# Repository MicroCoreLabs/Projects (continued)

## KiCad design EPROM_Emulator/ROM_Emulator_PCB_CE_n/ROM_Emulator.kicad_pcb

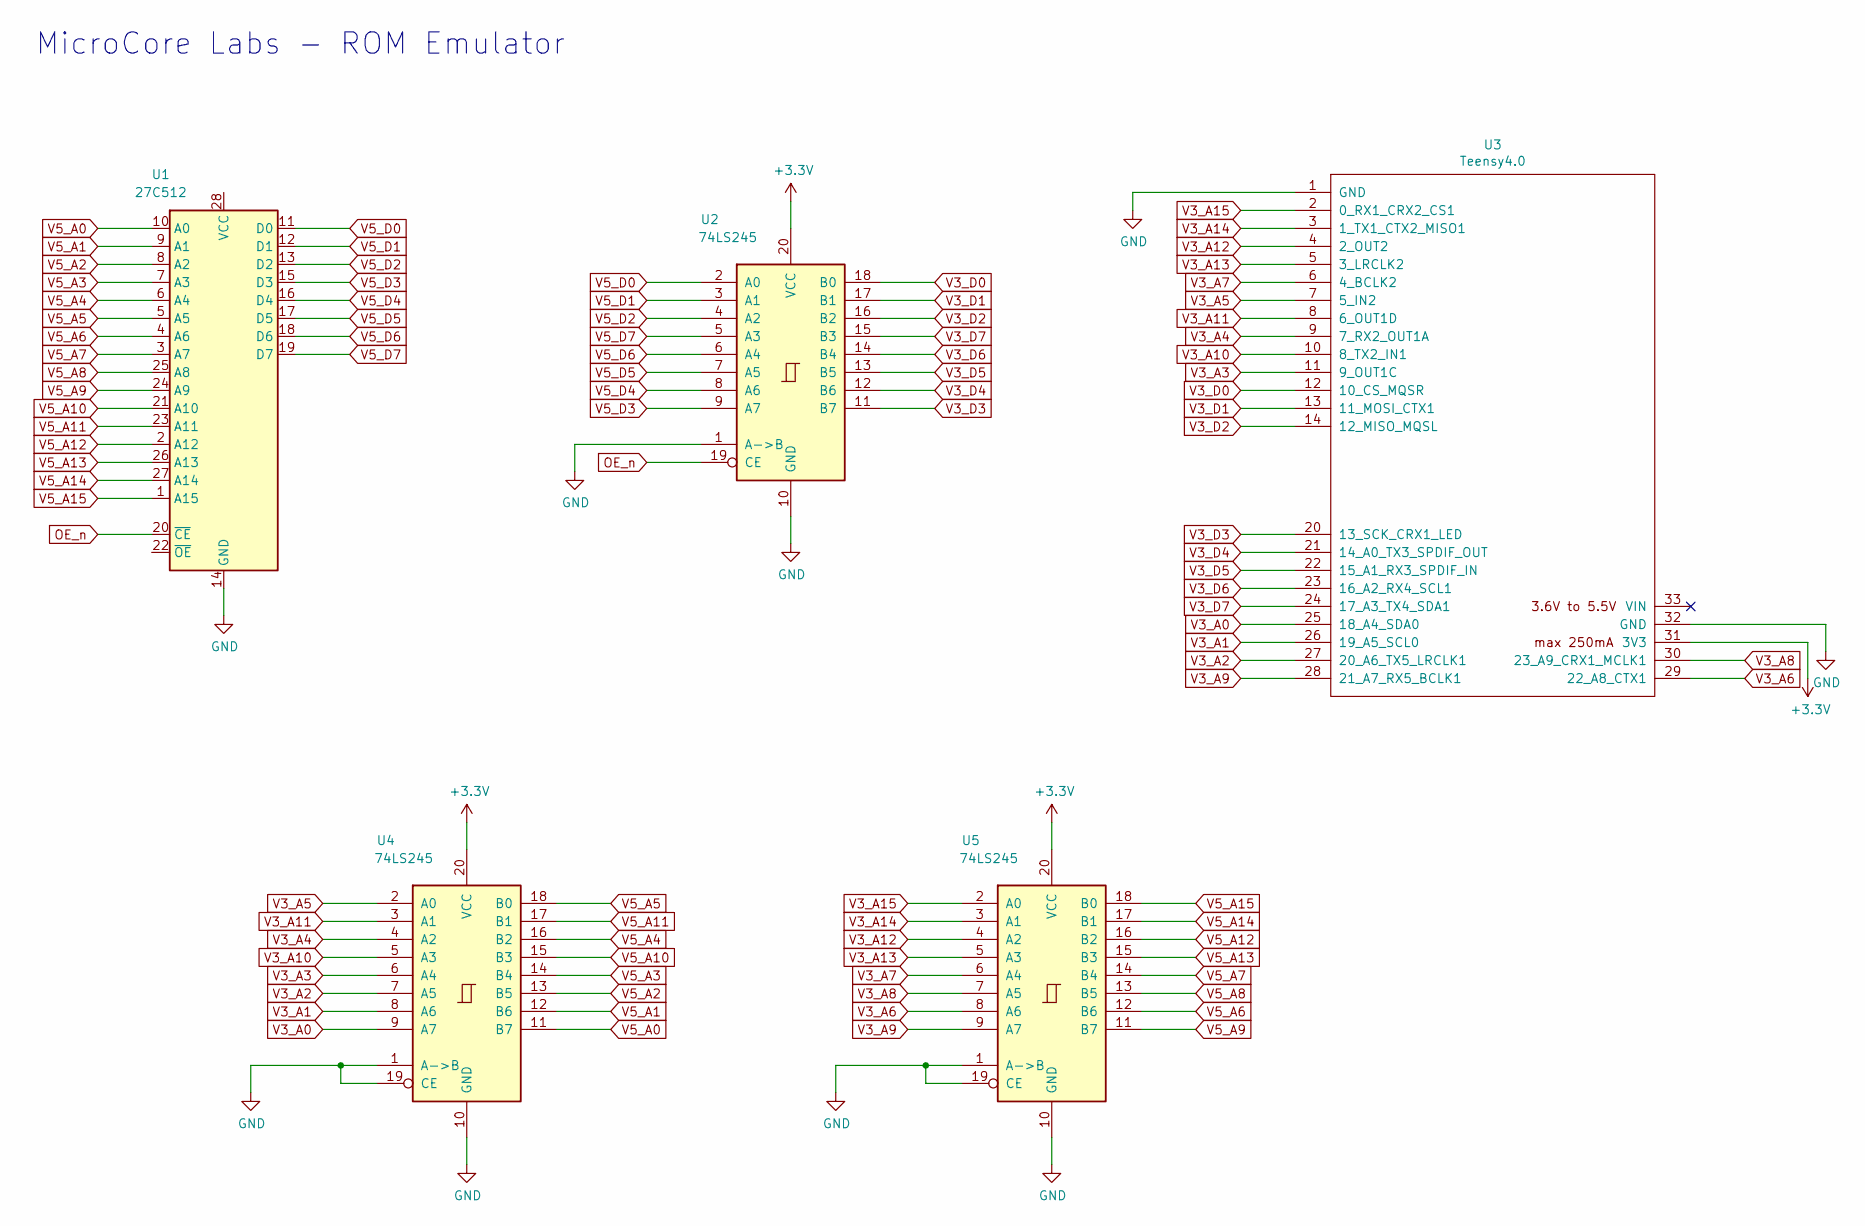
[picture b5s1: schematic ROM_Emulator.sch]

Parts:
U1: 27C512; DIP-28_W15.24mm
U2, U4, U5: 74LS245; SSOP-20_5.3x7.2mm_P0.65mm
U3: Teensy4.0; Teensy40

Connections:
+3V3: U2.20 (VCC), U3.31 (3V3), U4.20 (VCC), U5.20 (VCC)
GND: U1.14 (GND), U2.1 (A->B), U2.10 (GND), U3.1 (GND), U3.32 (GND), U4.1 (A->B), U4.10 (GND), U4.19 (CE), U5.1 (A->B), U5.10 (GND), U5.19 (CE)
OE_n: U1.20 (~CE), U2.19 (CE)
V3_A0: U3.25 (18_A4_SDA0), U4.9 (A7)
V3_A1: U3.26 (19_A5_SCL0), U4.8 (A6)
V3_A2: U3.27 (20_A6_TX5_LRCLK1), U4.7 (A5)
V3_A3: U3.11 (9_OUT1C), U4.6 (A4)
V3_A4: U3.9 (7_RX2_OUT1A), U4.4 (A2)
V3_A5: U3.7 (5_IN2), U4.2 (A0)
V3_A6: U3.29 (22_A8_CTX1), U5.8 (A6)
V3_A7: U3.6 (4_BCLK2), U5.6 (A4)
V3_A8: U3.30 (23_A9_CRX1_MCLK1), U5.7 (A5)
V3_A9: U3.28 (21_A7_RX5_BCLK1), U5.9 (A7)
V3_A10: U3.10 (8_TX2_IN1), U4.5 (A3)
V3_A11: U3.8 (6_OUT1D), U4.3 (A1)
V3_A12: U3.4 (2_OUT2), U5.4 (A2)
V3_A13: U3.5 (3_LRCLK2), U5.5 (A3)
V3_A14: U3.3 (1_TX1_CTX2_MISO1), U5.3 (A1)
V3_A15: U3.2 (0_RX1_CRX2_CS1), U5.2 (A0)
V3_D0: U2.18 (B0), U3.12 (10_CS_MQSR)
V3_D1: U2.17 (B1), U3.13 (11_MOSI_CTX1)
V3_D2: U2.16 (B2), U3.14 (12_MISO_MQSL)
V3_D3: U2.11 (B7), U3.20 (13_SCK_CRX1_LED)
V3_D4: U2.12 (B6), U3.21 (14_A0_TX3_SPDIF_OUT)
V3_D5: U2.13 (B5), U3.22 (15_A1_RX3_SPDIF_IN)
V3_D6: U2.14 (B4), U3.23 (16_A2_RX4_SCL1)
V3_D7: U2.15 (B3), U3.24 (17_A3_TX4_SDA1)
V5_A0: U1.10 (A0), U4.11 (B7)
V5_A1: U1.9 (A1), U4.12 (B6)
V5_A2: U1.8 (A2), U4.13 (B5)
V5_A3: U1.7 (A3), U4.14 (B4)
V5_A4: U1.6 (A4), U4.16 (B2)
V5_A5: U1.5 (A5), U4.18 (B0)
V5_A6: U1.4 (A6), U5.12 (B6)
V5_A7: U1.3 (A7), U5.14 (B4)
V5_A8: U1.25 (A8), U5.13 (B5)
V5_A9: U1.24 (A9), U5.11 (B7)
V5_A10: U1.21 (A10), U4.15 (B3)
V5_A11: U1.23 (A11), U4.17 (B1)
V5_A12: U1.2 (A12), U5.16 (B2)
V5_A13: U1.26 (A13), U5.15 (B3)
V5_A14: U1.27 (A14), U5.17 (B1)
V5_A15: U1.1 (A15), U5.18 (B0)
V5_D0: U1.11 (D0), U2.2 (A0)
V5_D1: U1.12 (D1), U2.3 (A1)
V5_D2: U1.13 (D2), U2.4 (A2)
V5_D3: U1.15 (D3), U2.9 (A7)
V5_D4: U1.16 (D4), U2.8 (A6)
V5_D5: U1.17 (D5), U2.7 (A5)
V5_D6: U1.18 (D6), U2.6 (A4)
V5_D7: U1.19 (D7), U2.5 (A3)

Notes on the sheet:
MicroCore Labs - ROM Emulator

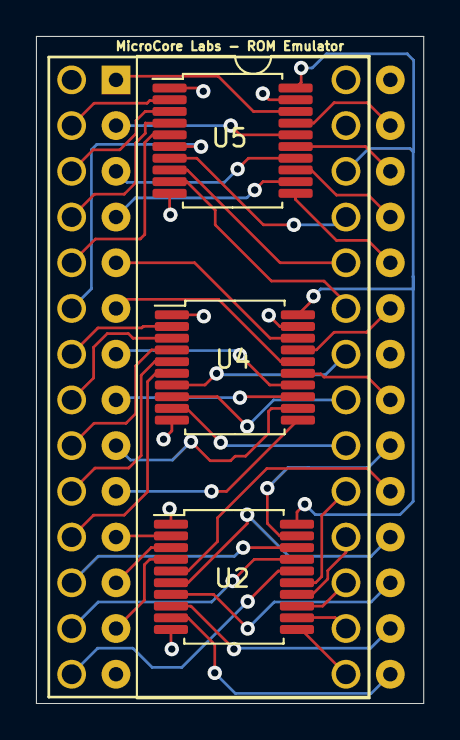
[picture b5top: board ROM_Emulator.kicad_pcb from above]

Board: 2 copper layers, 21.5 x 37.1 mm, 5 parts (0 on the bottom side), 51 nets.

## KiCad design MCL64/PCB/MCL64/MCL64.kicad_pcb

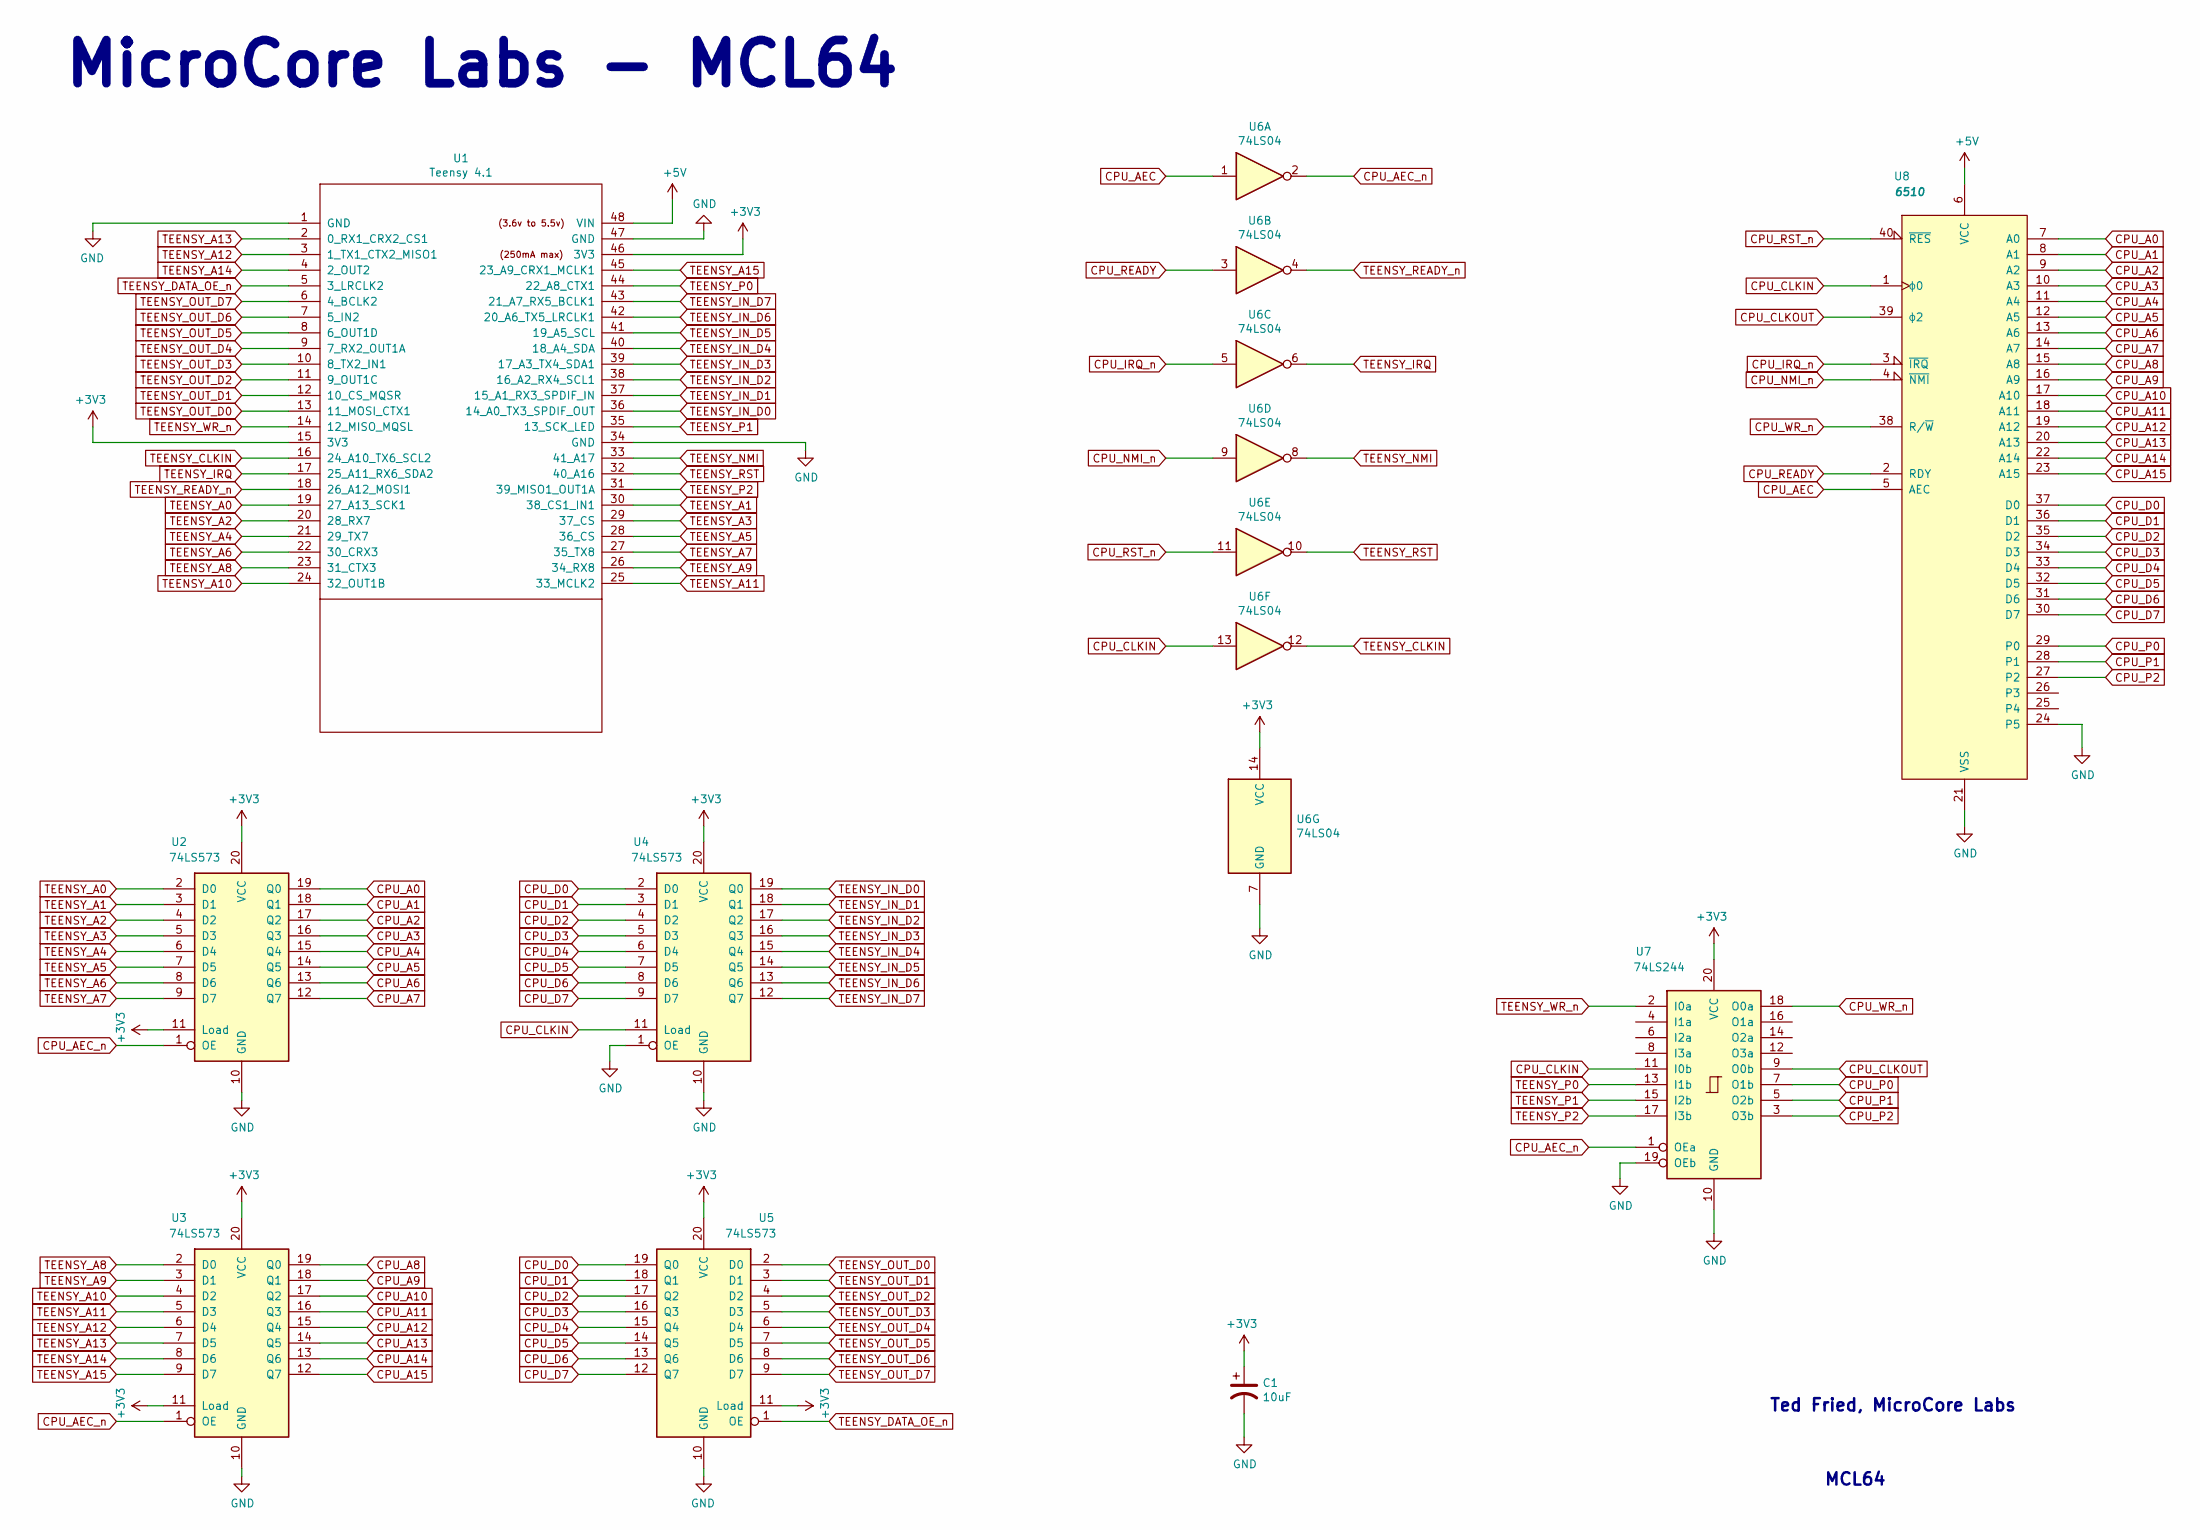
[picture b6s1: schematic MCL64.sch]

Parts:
C1: 10uF; C_Disc_D7.0mm_W2.5mm_P5.00mm
U1: Teensy 4.1; Teensy41_Ted_Modified
U2, U3, U4, U5: 74LS573; SSOP-20_5.3x7.2mm_P0.65mm
U6: 74LS04; SSOP-14_5.3x6.2mm_P0.65mm
U7: 74LS244; SSOP-20_5.3x7.2mm_P0.65mm
U8: 6510; DIP-40_W15.24mm

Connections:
+3V3: C1.1, U1.15 (3V3), U1.46 (3V3), U2.11 (Load), U2.20 (VCC), U3.11 (Load), U3.20 (VCC), U4.20 (VCC), U5.11 (Load), U5.20 (VCC), U6.14 (VCC), U7.20 (VCC)
+5V: U1.48 (VIN), U8.6 (VCC)
CPU_A0: U2.19 (Q0), U8.7 (A0)
CPU_A1: U2.18 (Q1), U8.8 (A1)
CPU_A2: U2.17 (Q2), U8.9 (A2)
CPU_A3: U2.16 (Q3), U8.10 (A3)
CPU_A4: U2.15 (Q4), U8.11 (A4)
CPU_A5: U2.14 (Q5), U8.12 (A5)
CPU_A6: U2.13 (Q6), U8.13 (A6)
CPU_A7: U2.12 (Q7), U8.14 (A7)
CPU_A8: U3.19 (Q0), U8.15 (A8)
CPU_A9: U3.18 (Q1), U8.16 (A9)
CPU_A10: U3.17 (Q2), U8.17 (A10)
CPU_A11: U3.16 (Q3), U8.18 (A11)
CPU_A12: U3.15 (Q4), U8.19 (A12)
CPU_A13: U3.14 (Q5), U8.20 (A13)
CPU_A14: U3.13 (Q6), U8.22 (A14)
CPU_A15: U3.12 (Q7), U8.23 (A15)
CPU_AEC: U6.1, U8.5 (AEC)
CPU_AEC_n: U2.1 (OE), U3.1 (OE), U6.2, U7.1 (OEa)
CPU_CLKIN: U4.11 (Load), U6.13, U7.11 (I0b), U8.1 (ϕ0)
CPU_CLKOUT: U7.9 (O0b), U8.39 (ϕ2)
CPU_D0: U4.2 (D0), U5.19 (Q0), U8.37 (D0)
CPU_D1: U4.3 (D1), U5.18 (Q1), U8.36 (D1)
CPU_D2: U4.4 (D2), U5.17 (Q2), U8.35 (D2)
CPU_D3: U4.5 (D3), U5.16 (Q3), U8.34 (D3)
CPU_D4: U4.6 (D4), U5.15 (Q4), U8.33 (D4)
CPU_D5: U4.7 (D5), U5.14 (Q5), U8.32 (D5)
CPU_D6: U4.8 (D6), U5.13 (Q6), U8.31 (D6)
CPU_D7: U4.9 (D7), U5.12 (Q7), U8.30 (D7)
CPU_IRQ_n: U6.5, U8.3 (~IRQ)
CPU_NMI_n: U6.9, U8.4 (~NMI)
CPU_P0: U7.7 (O1b), U8.29 (P0)
CPU_P1: U7.5 (O2b), U8.28 (P1)
CPU_P2: U7.3 (O3b), U8.27 (P2)
CPU_READY: U6.3, U8.2 (RDY)
CPU_RST_n: U6.11, U8.40 (~RES)
CPU_WR_n: U7.18 (O0a), U8.38 (R/~W)
GND: C1.2, U1.1 (GND), U1.34 (GND), U1.47 (GND), U2.10 (GND), U3.10 (GND), U4.1 (OE), U4.10 (GND), U5.10 (GND), U6.7 (GND), U7.10 (GND), U7.19 (OEb), U8.21 (VSS), U8.24 (P5)
TEENSY_A0: U1.19 (27_A13_SCK1), U2.2 (D0)
TEENSY_A1: U1.30 (38_CS1_IN1), U2.3 (D1)
TEENSY_A2: U1.20 (28_RX7), U2.4 (D2)
TEENSY_A3: U1.29 (37_CS), U2.5 (D3)
TEENSY_A4: U1.21 (29_TX7), U2.6 (D4)
TEENSY_A5: U1.28 (36_CS), U2.7 (D5)
TEENSY_A6: U1.22 (30_CRX3), U2.8 (D6)
TEENSY_A7: U1.27 (35_TX8), U2.9 (D7)
TEENSY_A8: U1.23 (31_CTX3), U3.2 (D0)
TEENSY_A9: U1.26 (34_RX8), U3.3 (D1)
TEENSY_A10: U1.24 (32_OUT1B), U3.4 (D2)
TEENSY_A11: U1.25 (33_MCLK2), U3.5 (D3)
TEENSY_A12: U1.3 (1_TX1_CTX2_MISO1), U3.6 (D4)
TEENSY_A13: U1.2 (0_RX1_CRX2_CS1), U3.7 (D5)
TEENSY_A14: U1.4 (2_OUT2), U3.8 (D6)
TEENSY_A15: U1.45 (23_A9_CRX1_MCLK1), U3.9 (D7)
TEENSY_CLKIN: U1.16 (24_A10_TX6_SCL2), U6.12
TEENSY_DATA_OE_n: U1.5 (3_LRCLK2), U5.1 (OE)
TEENSY_IN_D0: U1.36 (14_A0_TX3_SPDIF_OUT), U4.19 (Q0)
TEENSY_IN_D1: U1.37 (15_A1_RX3_SPDIF_IN), U4.18 (Q1)
TEENSY_IN_D2: U1.38 (16_A2_RX4_SCL1), U4.17 (Q2)
TEENSY_IN_D3: U1.39 (17_A3_TX4_SDA1), U4.16 (Q3)
TEENSY_IN_D4: U1.40 (18_A4_SDA), U4.15 (Q4)
TEENSY_IN_D5: U1.41 (19_A5_SCL), U4.14 (Q5)
TEENSY_IN_D6: U1.42 (20_A6_TX5_LRCLK1), U4.13 (Q6)
TEENSY_IN_D7: U1.43 (21_A7_RX5_BCLK1), U4.12 (Q7)
TEENSY_IRQ: U1.17 (25_A11_RX6_SDA2), U6.6
TEENSY_NMI: U1.33 (41_A17), U6.8
TEENSY_OUT_D0: U1.13 (11_MOSI_CTX1), U5.2 (D0)
TEENSY_OUT_D1: U1.12 (10_CS_MQSR), U5.3 (D1)
TEENSY_OUT_D2: U1.11 (9_OUT1C), U5.4 (D2)
TEENSY_OUT_D3: U1.10 (8_TX2_IN1), U5.5 (D3)
TEENSY_OUT_D4: U1.9 (7_RX2_OUT1A), U5.6 (D4)
TEENSY_OUT_D5: U1.8 (6_OUT1D), U5.7 (D5)
TEENSY_OUT_D6: U1.7 (5_IN2), U5.8 (D6)
TEENSY_OUT_D7: U1.6 (4_BCLK2), U5.9 (D7)
TEENSY_P0: U1.44 (22_A8_CTX1), U7.13 (I1b)
TEENSY_P1: U1.35 (13_SCK_LED), U7.15 (I2b)
TEENSY_P2: U1.31 (39_MISO1_OUT1A), U7.17 (I3b)
TEENSY_READY_n: U1.18 (26_A12_MOSI1), U6.4
TEENSY_RST: U1.32 (40_A16), U6.10
TEENSY_WR_n: U1.14 (12_MISO_MQSL), U7.2 (I0a)

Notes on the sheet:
MicroCore Labs - MCL64
Ted Fried, MicroCore Labs
MCL64

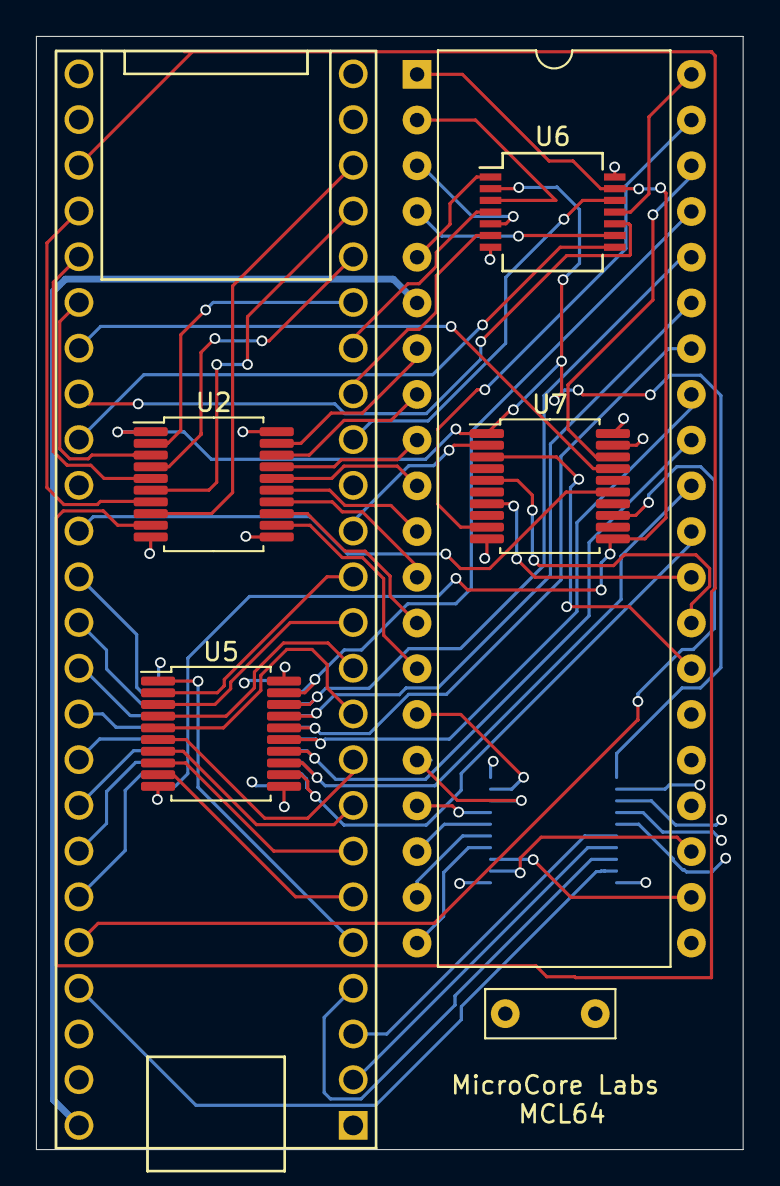
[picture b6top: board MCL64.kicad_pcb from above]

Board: 4 copper layers, 39.3 x 61.8 mm, 9 parts (0 on the bottom side), 81 nets.

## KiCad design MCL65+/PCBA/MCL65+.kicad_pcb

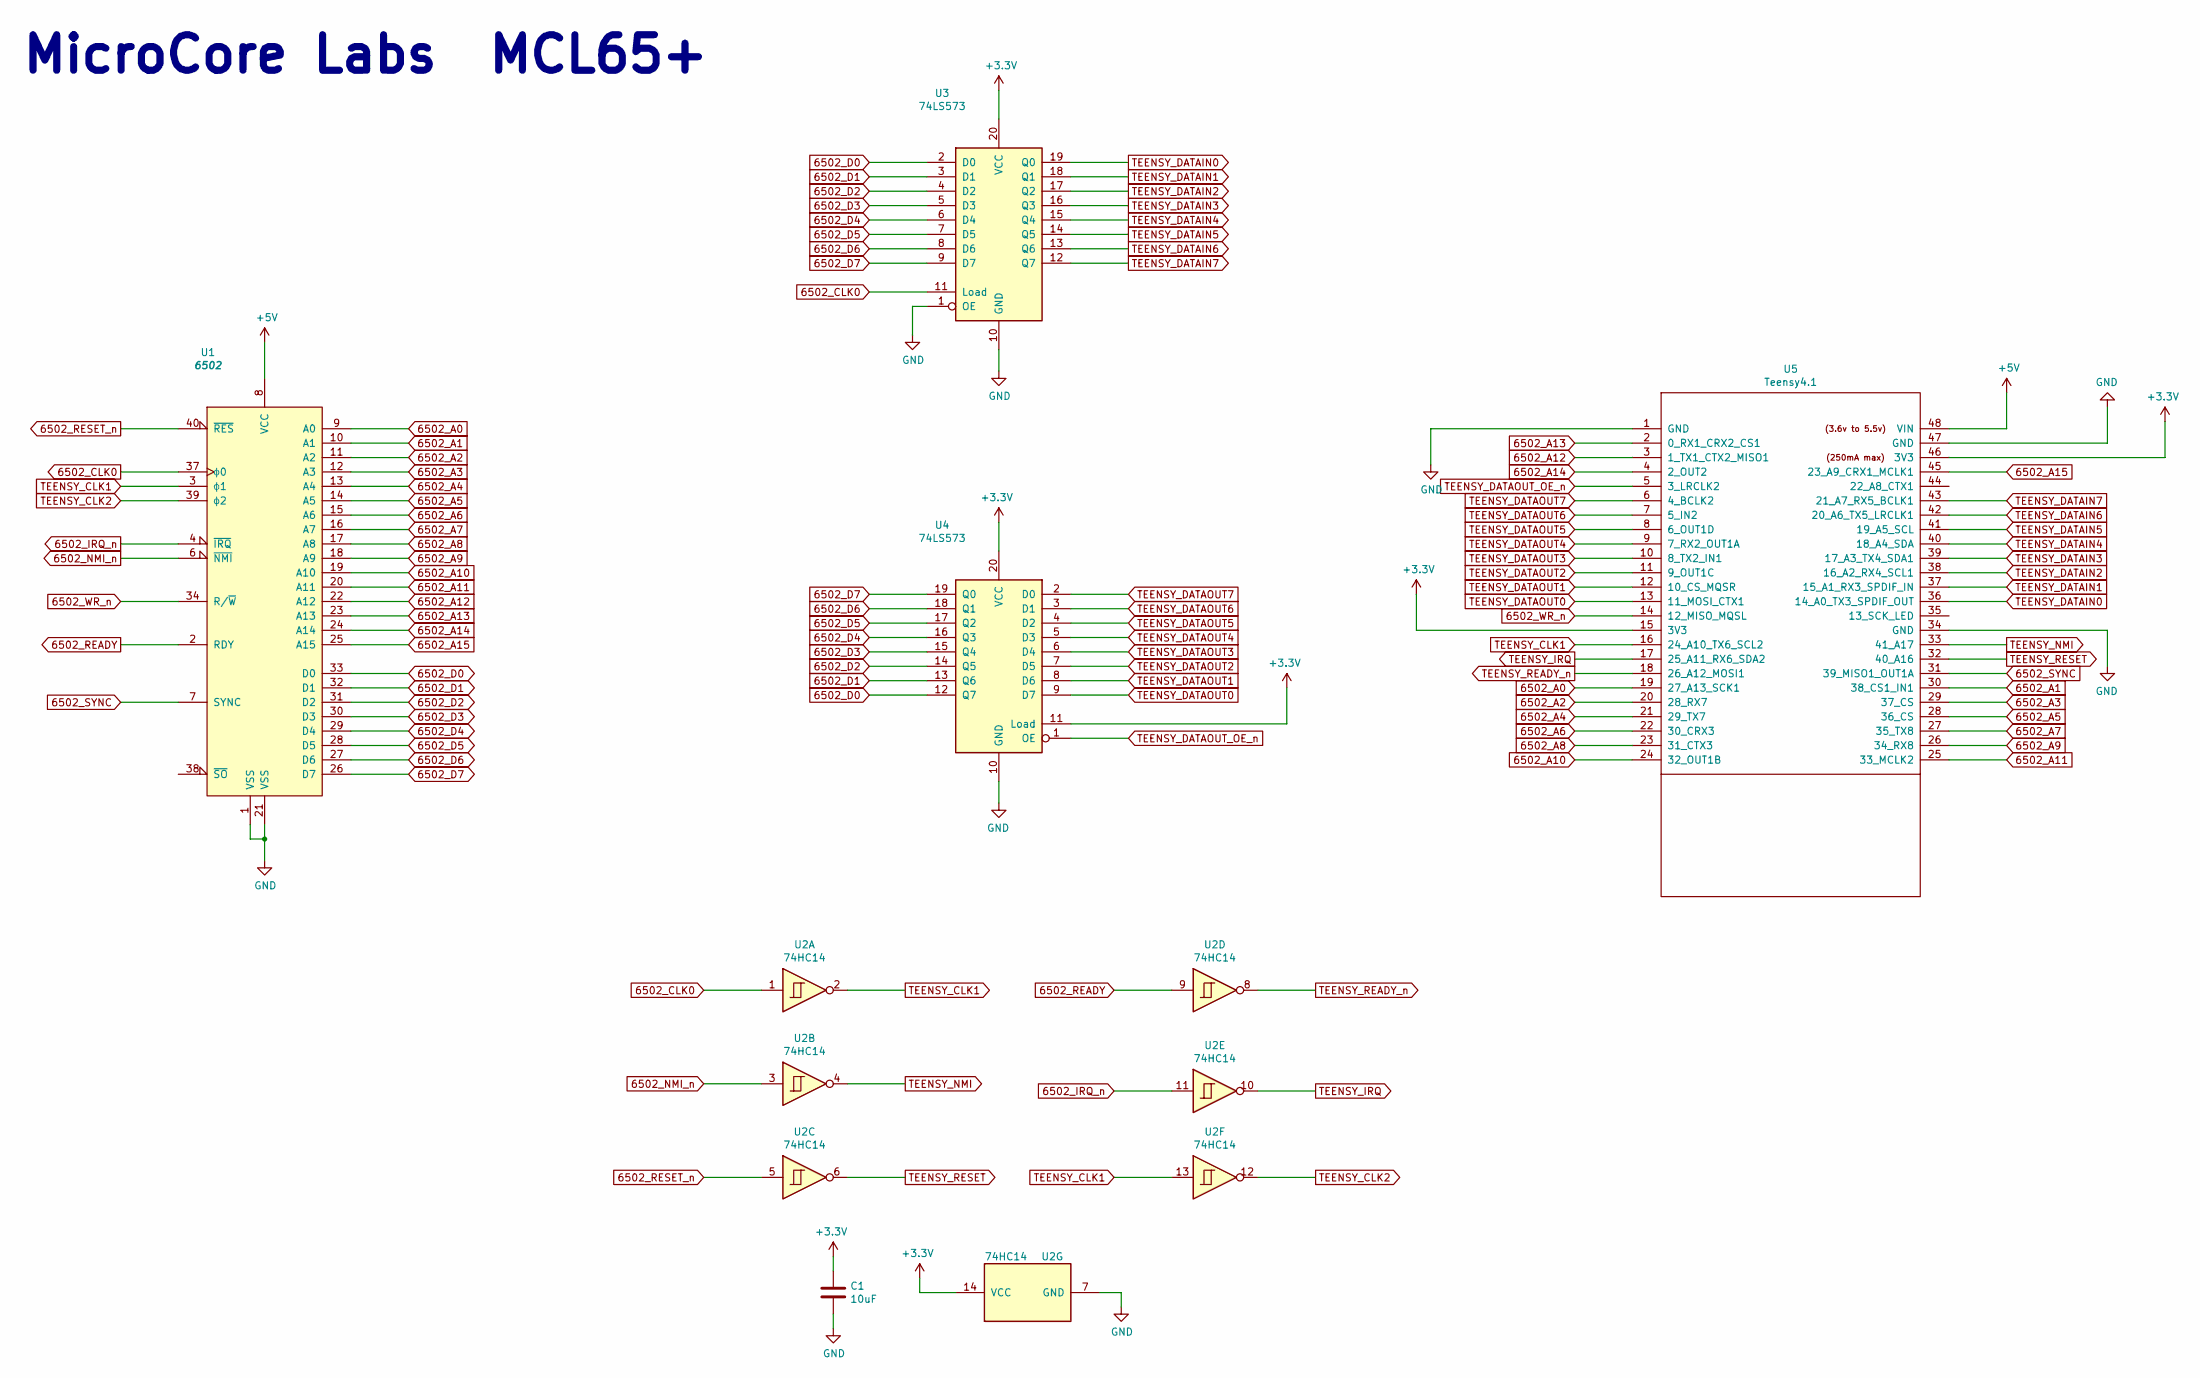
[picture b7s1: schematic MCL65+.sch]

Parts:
C1: 10uF; C_Disc_D7.0mm_W2.5mm_P5.00mm
U1: 6502; DIP-40_W15.24mm
U2: 74HC14; DIP-14_W7.62mm_Socket
U3, U4: 74LS573; DIP-20_W7.62mm_Socket
U5: Teensy4.1; Teensy41

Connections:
6502_A0: U1.9 (A0), U5.19 (27_A13_SCK1)
6502_A1: U1.10 (A1), U5.30 (38_CS1_IN1)
6502_A2: U1.11 (A2), U5.20 (28_RX7)
6502_A3: U1.12 (A3), U5.29 (37_CS)
6502_A4: U1.13 (A4), U5.21 (29_TX7)
6502_A5: U1.14 (A5), U5.28 (36_CS)
6502_A6: U1.15 (A6), U5.22 (30_CRX3)
6502_A7: U1.16 (A7), U5.27 (35_TX8)
6502_A8: U1.17 (A8), U5.23 (31_CTX3)
6502_A9: U1.18 (A9), U5.26 (34_RX8)
6502_A10: U1.19 (A10), U5.24 (32_OUT1B)
6502_A11: U1.20 (A11), U5.25 (33_MCLK2)
6502_A12: U1.22 (A12), U5.3 (1_TX1_CTX2_MISO1)
6502_A13: U1.23 (A13), U5.2 (0_RX1_CRX2_CS1)
6502_A14: U1.24 (A14), U5.4 (2_OUT2)
6502_A15: U1.25 (A15), U5.45 (23_A9_CRX1_MCLK1)
6502_CLK0: U1.37 (ϕ0), U2.1, U3.11 (Load)
6502_D0: U1.33 (D0), U3.2 (D0), U4.12 (Q7)
6502_D1: U1.32 (D1), U3.3 (D1), U4.13 (Q6)
6502_D2: U1.31 (D2), U3.4 (D2), U4.14 (Q5)
6502_D3: U1.30 (D3), U3.5 (D3), U4.15 (Q4)
6502_D4: U1.29 (D4), U3.6 (D4), U4.16 (Q3)
6502_D5: U1.28 (D5), U3.7 (D5), U4.17 (Q2)
6502_D6: U1.27 (D6), U3.8 (D6), U4.18 (Q1)
6502_D7: U1.26 (D7), U3.9 (D7), U4.19 (Q0)
6502_IRQ_n: U1.4 (~IRQ), U2.11
6502_NMI_n: U1.6 (~NMI), U2.3
6502_READY: U1.2 (RDY), U2.9
6502_RESET_n: U1.40 (~RES), U2.5
6502_SYNC: U1.7 (SYNC), U5.31 (39_MISO1_OUT1A)
6502_WR_n: U1.34 (R/~W), U5.14 (12_MISO_MQSL)
+3V3: C1.1, U2.14 (VCC), U3.20 (VCC), U4.11 (Load), U4.20 (VCC), U5.15 (3V3), U5.46 (3V3)
+5V: U1.8 (VCC), U5.48 (VIN)
GND: C1.2, U1.1 (VSS), U1.21 (VSS), U2.7 (GND), U3.1 (OE), U3.10 (GND), U4.10 (GND), U5.1 (GND), U5.34 (GND), U5.47 (GND)
TEENSY_CLK1: U1.3 (ϕ1), U2.2, U2.13, U5.16 (24_A10_TX6_SCL2)
TEENSY_CLK2: U1.39 (ϕ2), U2.12
TEENSY_DATAIN0: U3.19 (Q0), U5.36 (14_A0_TX3_SPDIF_OUT)
TEENSY_DATAIN1: U3.18 (Q1), U5.37 (15_A1_RX3_SPDIF_IN)
TEENSY_DATAIN2: U3.17 (Q2), U5.38 (16_A2_RX4_SCL1)
TEENSY_DATAIN3: U3.16 (Q3), U5.39 (17_A3_TX4_SDA1)
TEENSY_DATAIN4: U3.15 (Q4), U5.40 (18_A4_SDA)
TEENSY_DATAIN5: U3.14 (Q5), U5.41 (19_A5_SCL)
TEENSY_DATAIN6: U3.13 (Q6), U5.42 (20_A6_TX5_LRCLK1)
TEENSY_DATAIN7: U3.12 (Q7), U5.43 (21_A7_RX5_BCLK1)
TEENSY_DATAOUT0: U4.9 (D7), U5.13 (11_MOSI_CTX1)
TEENSY_DATAOUT1: U4.8 (D6), U5.12 (10_CS_MQSR)
TEENSY_DATAOUT2: U4.7 (D5), U5.11 (9_OUT1C)
TEENSY_DATAOUT3: U4.6 (D4), U5.10 (8_TX2_IN1)
TEENSY_DATAOUT4: U4.5 (D3), U5.9 (7_RX2_OUT1A)
TEENSY_DATAOUT5: U4.4 (D2), U5.8 (6_OUT1D)
TEENSY_DATAOUT6: U4.3 (D1), U5.7 (5_IN2)
TEENSY_DATAOUT7: U4.2 (D0), U5.6 (4_BCLK2)
TEENSY_DATAOUT_OE_n: U4.1 (OE), U5.5 (3_LRCLK2)
TEENSY_IRQ: U2.10, U5.17 (25_A11_RX6_SDA2)
TEENSY_NMI: U2.4, U5.33 (41_A17)
TEENSY_READY_n: U2.8, U5.18 (26_A12_MOSI1)
TEENSY_RESET: U2.6, U5.32 (40_A16)

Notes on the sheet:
MicroCore Labs MCL65+

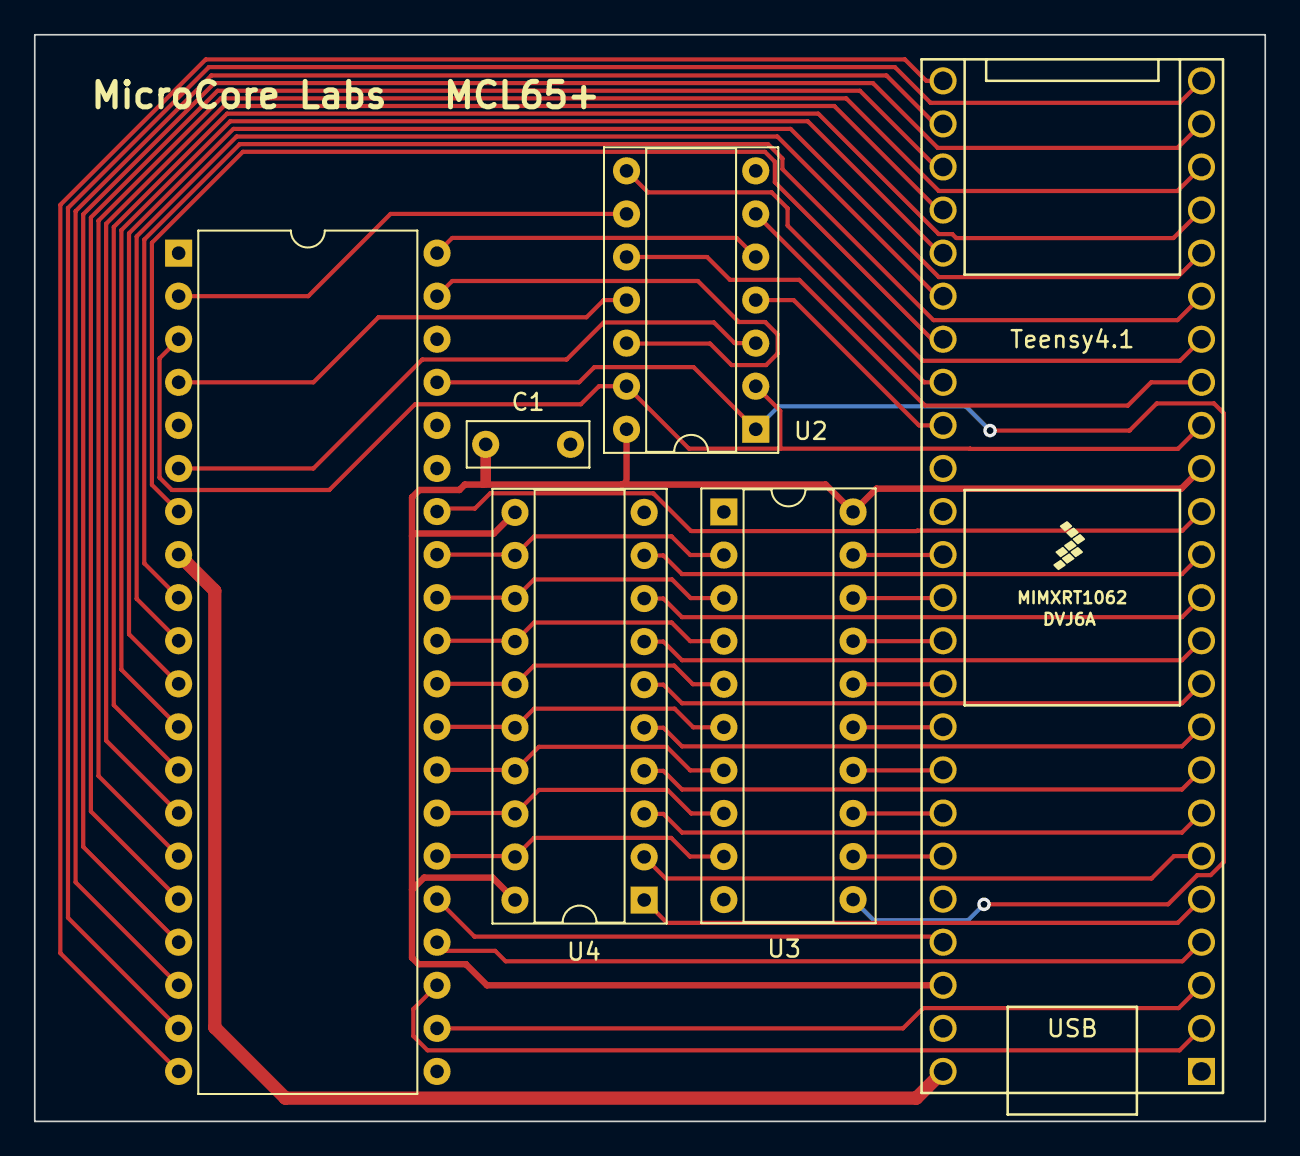
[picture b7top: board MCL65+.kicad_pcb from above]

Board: 2 copper layers, 72.6 x 64.1 mm, 6 parts (0 on the bottom side), 57 nets.

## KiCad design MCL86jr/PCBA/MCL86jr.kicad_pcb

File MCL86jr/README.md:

# MCL86jr Accelerator Board

This board is a drop-in replacement for the 8088 CPU inside of the PCjr.  It utilizes a Xilinx Spartan-6 FPGA and 512KB of SRAM.

The CPU core is the MCL86 and can be run in cycle accurare mode which boosts PCjr performance by almost 6X which is close to the speed of an 8Mhz IBM PC AT!

The board schematic and layout were done using KiCad and all of the development files are in the PCBA directory. The board was manufacured and assembled by PCBWay.

Updated on 4/15/2025
- Microcode and EU files updated to integrate bug fixes found in the MCL86 on the MiSTer PCXT project
- FPGA Configuration Files folder added which contains the FPGA direct programming .bit file and also the configuration Flash .mc file

For questions email me at www.MicroCoreLabs.com

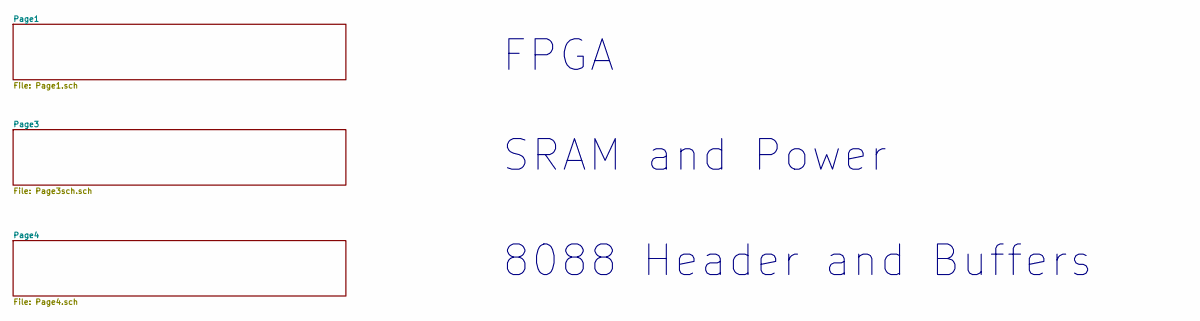
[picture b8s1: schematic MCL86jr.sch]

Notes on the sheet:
FPGA
SRAM and Power
8088 Header and Buffers

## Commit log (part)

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2019-10-14 Uploaded 10_13_2019
2019-10-14 Uploaded 10_14_2019
2019-10-19 Uploaded 10_19_2019
2019-10-20 Uploaded 10_20_2019
2019-11-03 Uploaded 11_3_2019
2019-11-10 Uploaded 11_9_2019
2019-11-26 Uploaded 11/25/2019
2019-11-26 Uploaded 11_25_2019
2019-12-11 Uploaded 12_10_2019
2019-12-25 Uploaded 12_24_2019
2020-01-25 Uploaded_1_25_2020
2020-02-18 Uploaded_2_17_2020
2020-02-23 Uploaded_2_23_2020
2020-03-23 Uploaded_3_22_2020
2020-03-31 Uploaded_3_30_2020
2020-04-03 Uploaded_4_3_2020
2020-07-14 Uploaded 7_14_2020
2020-08-29 Uploaded_8_28_2020
2020-11-12 Uploaded_11_11_2020
2021-01-07 Uploaded_1_6_2021
2021-02-21 Uploaded_2_20_2021
2021-03-21 Uploaded 3_20_2021
2021-03-21 Uploaded 3_21_2021
2021-03-21 Uploaded 3_21_21
2021-04-22 Uploaded 4/22/2021
2021-09-15 Uploaded_9_14_2021
2021-09-24 Uploaded_9_23_2021
2021-09-30 Uploaded_9_30_2021
2021-10-15 Create BILL_OF_MATERIALS.TXT
    Uploaded_10_15_2021
2021-11-12 Add dynamic mode change by writing to $d030
2021-11-14 This would prevent writes to byte 0x02
2021-11-14 Use current_p to test for which ROM and IO mode currently is in effect and test those modes before effecuating mode change at d030
2021-11-14 Bah, did not compile test, fixed defines and if() logic
2021-11-22 Uploaded_11_21_2021
2021-11-29 Uploaded_11_28_2021
2021-12-13 Uploaded_12_12_2021
2022-02-01 Uploaded_1_31_2022
2022-02-14 Uploaded_2_14_2022
2022-05-14 Uploaded_5_14_2022
2022-05-25 Uploaded_5_25_2022
2022-07-18 Uploaded 7_17_2022
2022-07-31 Uploaded_7_30_2022
2022-08-21 Uploaded_8_20_2022
2022-08-22 Uploaded_8_21_2022
2022-10-01 Uploaded_10_1_2022
2022-10-30 Uploaded 10_30_2022
2022-11-06 Uploaded_11_5_2022
2022-11-06 Uploaded_11_6_2022
2022-12-03 Uploaded_12_2_2022
2022-12-04 Uploaded_12_3_2022
2022-12-05 Uploaded_12_5_2022
2022-12-26 Uploaded_12_25_2022
2022-12-28 Uploaded_12_28_2022
2023-01-29 Uploaded_1_28_2023
2023-04-13 Uploaded_4_12_2023
2023-04-30 Uploaded_4_30_2023
2023-05-05 Uploaded_5_5_2023
2023-05-06 added debugger version of Z80 code
2023-05-15 Uploaded_5_14_2023
2023-06-03 Changed_6_2_2023
2023-07-12 Uploaded_7_12_2023
2023-09-02 Uploaded_9_1_2023
2023-10-26 Uploaded_10_25_2023
2023-10-29 Uploaded_10_29_2023
2024-07-18 Uploaded_7_18_2024
2024-07-19 Uploaded_7_19_2024
2024-07-22 Uploaded_7_22_2024
2024-09-08 UPLOADED_9_7_2024
2024-10-06 Uploaded 10_5_2024
2024-10-12 Uploaded 10_11_2024
2024-10-29 Add build script for LTEMM.
2024-10-29 Add DOSBox and TASM for build.
2024-10-29 Add gitattributes to handle line endings.
2024-10-29 Import the unmodified LTEMM source.
    From https://www.lo-tech.co.uk/wiki/LTEMM.EXE.
2024-10-29 Modity LTEMM driver for XTMax.
2024-10-29 Add Borland C++ 3.1 (Minimal) for build.
2024-10-29 Add build script for SDPP.
2024-10-29 Import the unmodified SDPP source.
    From https://forum.vcfed.org/index.php?threads/sd-card-to-parallel-port-driver-for-msdos-ver-1-1.42008/.
2024-10-29 Modify SDPP driver for XTMax.
2024-11-03 Commit pre-built binaries for LTEMM and SDPP.
2024-11-07 Uploaded_11_6_2024
2024-11-11 Uploaded_11_11_2024
2024-11-12 Uploaded_11_12_2024
2024-11-16 Reorganize the drivers into a new folder.
2024-11-17 Uploaded_11_16_2024
2024-11-17 Add LTEMM and SDPP drivers for XTMax (#27)
    * Add gitattributes to handle line endings.
    * Import the unmodified LTEMM source.
    From https://www.lo-tech.co.uk/wiki/LTEMM.EXE.
    * Add DOSBox and TASM for build.
    * Add build script for LTEMM.
    * Modity LTEMM driver for XTMax.
2024-11-26 Uploaded_11_26_2024
2024-12-15 Uploaded_12_14_2024
2024-12-27 Uploaded_12_26_2024
2025-01-01 Mask unimplemented IOCTL message.
2025-01-01 Add build for 286+.
2025-01-01 Optimized IO for 8086.
2025-01-01 Adding pre-build drivers.
2025-01-04 Improvements to the SDPP driver. (#30)
    * Mask unimplemented IOCTL message.
    * Add build for 286+.
    * Optimized IO for 8086.
    * Adding pre-build drivers.
2025-01-05 Refactor SD driver the IO to XTMax.
2025-01-13 Refactor the EMS driver to support 8MB.
2025-01-20 Improvements to the SD Card and EMS drivers. (#31)
    * Refactor SD driver the IO to XTMax.
    * Refactor the EMS driver to support 8MB.
2025-01-20 Uploaded_1_20_2025
2025-01-26 Add NASM for build.
2025-01-26 Add BootROM support.
2025-02-09 Add INT13h handling for SD Card.
2025-02-09 Optimize for 80186-compatible.
2025-02-09 Some optimizations.
2025-02-09 Reduce wait from SD Card.
2025-02-09 Remove some of the debug features to make the code more readable.
2025-02-09 Bump maximum disk size to 8GB.
2025-02-10 Uploaded_2_9_2025
2025-02-16 Revert "Uploaded_2_9_2025"
    This reverts commit ec79bbdbc9052617461a3c1b4952290a05a51adb.
2025-02-16 Make the IO port base a define.
2025-02-16 Improve SD Card initialization logic.
2025-02-16 Improve timeout management logic.
2025-02-16 Fix CPU test to properly handle 808x vs V20.
2025-02-16 Fixing DEBUG_IO builds.
2025-02-16 Update XTSD to use MOVSW.
2025-02-16 Implementing a different test for processor type.
2025-02-16 Major rework of IO to use MOVSW.
2025-02-16 More code reorg and auto-detecting second drive.
2025-02-16 Allow swapping driver ID between the BIOS disk and XTMax.
2025-02-16 Fixing missing STI at the top of the handler.
2025-02-16 Implement INT18h bootstrapping.
2025-02-16 Allow use with another fixed drive (eg: ESDI drive).
2025-02-16 Fix address of the ROM segment.
2025-02-17 Add diagnostics program.
2025-02-17 Workaround for MS-DOS strange handling of interrupts.
2025-02-17 Make the BootROM relocatable.
2025-02-17 Use a lookup table for the memory map.
2025-02-17 Some more refactor of the Teensy code.
2025-02-17 Many fixes and improvements to the BIOS Extension ROM. (#33)
    * Revert "Uploaded_2_9_2025"
    This reverts commit ec79bbdbc9052617461a3c1b4952290a05a51adb.
    * Fixing DEBUG_IO builds.
    * Make the IO port base a define.
    * Fix CPU test to properly handle 808x vs V20.
    * Improve timeout management logic.
2025-02-18 Revert "Make the BootROM relocatable."
    This reverts commit fae52a005736c3f9e2208f9b77905f780a7aa7d9.
2025-02-18 Fix issue booting from other fixed disk.
2025-02-19 Revert "Some more refactor of the Teensy code."
    This reverts commit e03594b514b7d1e41af70f44ef220a1571d88deb.
2025-02-20 Fixes stability issue and booting from fixed disk. (#35)
    * Revert "Some more refactor of the Teensy code."
    This reverts commit e03594b514b7d1e41af70f44ef220a1571d88deb.
    * Fix issue booting from other fixed disk.
2025-02-22 Fix the XTEMM memory test to not emit speaker noise.
2025-02-27 Improvements to the bootstrap code.
2025-02-27 Improvements to the bootstrap code. (#37)
2025-02-27 Fix the XTEMM memory test to not emit speaker noise. (#36)
2025-02-27 Customize the UMB Driver prompts.
2025-02-27 Import unmodified USE!UMBS source.
    From https://forum.vcfed.org/index.php?threads/loading-dos-high-on-a-xt.32320/
2025-03-03 Refactor memory management. Allow activation of EMS/UMB on demand.
2025-03-07 Update the XTEMM and XTUMBS drivers to map their ranges.
2025-03-07 Add instructions for all the drivers.
2025-03-08 Add support for DOS Upper Memory Blocks (UMBs). (#38)
    * Import unmodified USE!UMBS source.
    From https://forum.vcfed.org/index.php?threads/loading-dos-high-on-a-xt.32320/
    * Customize the UMB Driver prompts.
    * Refactor memory management. Allow activation of EMS/UMB on demand.
    * Update the XTEMM and XTUMBS drivers to map their ranges.
    * Add instructions for all the drivers.
2025-04-04 Uploaded_4_3_2025
2025-04-16 Uploaded_4_15_2025
2025-07-03 Uploaded 7_2_2025
2025-07-05 Uploaded_7_4_2025
2025-07-09 Uploaded_7_9_2025
2025-07-14 Uploaded_7_14_2025
2025-09-30 Uploaded_9_29_2025
2025-10-05 Uploaded_10_4_2025
2025-11-13 Uploaded_11_13_2025
2025-11-21 Uploaded_11_21_2025
2025-12-15 Uploaded_12_15_2025
2025-12-17 Uploaded_12_16_2025
2025-12-17 Uploaded_12_17_2025
2025-12-23 Uploaded_12_23_2025
2025-12-28 Uploaded_12_27_2025
2026-01-07 Uploaded_1_6_2026
2026-01-14 Uploaded_1_14_2026
2026-01-18 Uploaded_1_18_2026
2026-01-21 Uploade_1_21_2026
2026-02-11 Uploaded_2_11_2026
2026-04-06 small changes for easier data manipulation
2026-04-07 changes to make debugger more useable
2026-05-10 BIU: stage CS register update so it commits atomically with pfq_addr_in
    JMP FAR / CALL FAR / RET FAR microcode strobes the BIU twice: first an
    "update CS" strobe (eu_biu_strobe=2'b11, code 3'h2), then the actual
    "jump request" (eu_biu_req_code=5'h19) which atomically updates
    pfq_addr_in to the new IP. Real 8088 microcode treats CS+IP as a single
    update from the BIU's point of view; MCL86jr's microcode strobes them
    separately, and without staging the BIU briefly sees new CS + old
2026-05-10 BIU: ack HALT immediately without running a bus cycle
    Real 8088 HALT is documented as one T1 phase (ALE pulse + S2:S0=011
    status) and does NOT wait for READY. The original BIU runs HALT
    through the normal data-bus states 0x02..0x0A, including the
    READY-wait at state 0x07. There is no architectural reason for a host
    platform to drive READY in response to a HALT cycle -- HLT is an
    internal CPU state, not a bus transaction that needs acknowledgment --
2026-05-10 Add microcode assembler
    Standalone Python tool that parses the `p`-line triplet format used by
    Microcode_MCL86.txt and emits a Xilinx .coe
    (memory_initialization_vector) file or a Verilog $readmemh .mem file.
    Usage:
    python3 MCL86/Core/ucode_assembler.py assemble Microcode_MCL86.txt \
    --coe MCL86_Microcode_Xilinx_Version_<N>.coe
2026-05-10 V5 microcode: STORE/RESTORE_SEG_PREFIX use r2 scratch, not AF flag
    The original procedures stashed the segment-override prefix bit in
    eu_flags bit 4 (AF) across the BIU operation. That corrupts the
    architectural AF on every string-op call site -- 8086 spec says string
    ops preserve flags, but every MOVS/LODS/CMPS would clear AF (path B,
    no override) or force-set it to 1 (path A, override). Manifests during
    PCjr BIOS POST: after `INC DI 0x4F->0x50` sets AF=1, the next MOVSW
2026-05-10 BIU: proper 8086 offset-wrap on word-read byte-2 address
    Real 8086 byte-2 rule: byte_2_linear = seg*16 + ((offset+1) & 0xFFFF).
    The offset wraps within the segment; the linear address does not. Two
    cases need to be handled correctly:
    - byte_1 at any 0x?FFFF linear address with a non-paragraph-aligned
    segment: byte_2 needs the carry past bit 15 to propagate through
    the upper 4 bits of addr_out_temp. Hit by code that does word
2026-05-10 V6 microcode: don't skip INT poll for non-SS segment loads
    Real 8086 delays interrupts by one instruction only after MOV/POP to
    SS (atomic stack reload paired with MOV SP, ...). MCL86jr's microcode
    applied that delay to all segment-register loads -- POP ES / POP CS /
    POP DS / MOV ES / MOV CS / MOV DS -- by routing them through the
    legacy 0x0470-0x0478 ending whose final jump goes to 0x0011 (skipping
    the 0x0006-0x000B interrupt-poll section of the main fetch loop). That
2026-05-19 V7 microcode + eu.v: IRET interrupt-recognition fix
    Real 8086 only delays interrupt recognition after STI / MOV SS / POP SS.
    MCL86jr was also deferring after IRET, which broke the BIOS timer ISR's
    return path: IRET pops FLAGS (with IF=1) and the very next 18.2Hz tick
    that lands during the return-from-ISR should be taken immediately.
    MCL86jr was skipping that poll and the tick got dropped until the next
    real new_instruction edge.
2026-05-21 V8 microcode: AAM/AAD flags from AL, not full AX
    AAM (0xD4) and AAD (0xD5) microcode populated alu_last_result with
    the full AX register and called All_Flags_WORD, which uses the 16-bit
    domain for SF (bit 15) and ZF (whole word). Per Intel docs, AAM/AAD
    set SF, ZF, PF on AL only (CF, OF, AF are undefined).
    For AAM, the post-instruction AX has AH=quotient, AL=remainder. When
    AL=0 but AH!=0 (e.g. AL_pre=0x50, AAM 10 -> AX=0x0800), All_Flags_WORD
2026-06-05 Uploaded_6_4_2025
2026-06-05 Uploaded_6_4_2026
